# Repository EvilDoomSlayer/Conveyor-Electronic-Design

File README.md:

# Conveyor-Electronic-Design

This repository contains the electronic design automation (EDA) files for the **Luggage Classification Conveyor** custom PCB. It is a submodule of the main firmware repository.

## Overview

This PCB consolidates the connections between the ESP32 microcontroller, the motor drivers, and the various sensors used in the sorting system. It replaces a breadboard setup to provide a robust and reliable connection for the sorting machinery.

## Project Contents

* **/KiCad_Project**: The full project folder containing:
    * `.kicad_sch`: The schematic file.
    * `.kicad_pcb`: The PCB layout file.
* **/Gerbers**: Production files generated for PCB fabrication (Zip file usually required by manufacturers like JLC or PCBWay).

## Schematic Details

The board is designed to interface with an **ESP32-WROOM-32** dev module.

### Key Interfaces
* **Power Input**: 5V DC (Powers the ESP32 and the Servos/DC Motor).
* **Motor Driver**: On-board socket for an **L293D** motor driver IC.
* **Sensor Headers**:
    * 3-pin headers for Servos (Signal, VCC, GND).
    * 4-pin header for HX711 (Load Cell Amplifier).
    * Digital headers for IR (E18-D80NK) and Magnetic (KY-024) sensors.

### Pinout Mapping
This PCB routes the ESP32 GPIOs strictly according to the firmware configuration:

| Component | ESP32 GPIO |
| :--- | :--- |
| **L293D (1A/2A)** | GPIO 16, 17 |
| **Load Cell (SCK/DT)** | GPIO 19, 23 |
| **Servos (1 & 2)** | GPIO 21, 22 |
| **Magnetic Sensor** | GPIO 32 |
| **IR Sensor** | GPIO 34 |

## Fabrication

The design is a 2-layer board. Standard manufacturing tolerances apply:
* **Thickness**: 1.6mm
* **Copper Weight**: 1oz
* **Solder Mask**: Green (or preferred color)

## Software Used

* **KiCad**: For Schematic capture and PCB Layout.

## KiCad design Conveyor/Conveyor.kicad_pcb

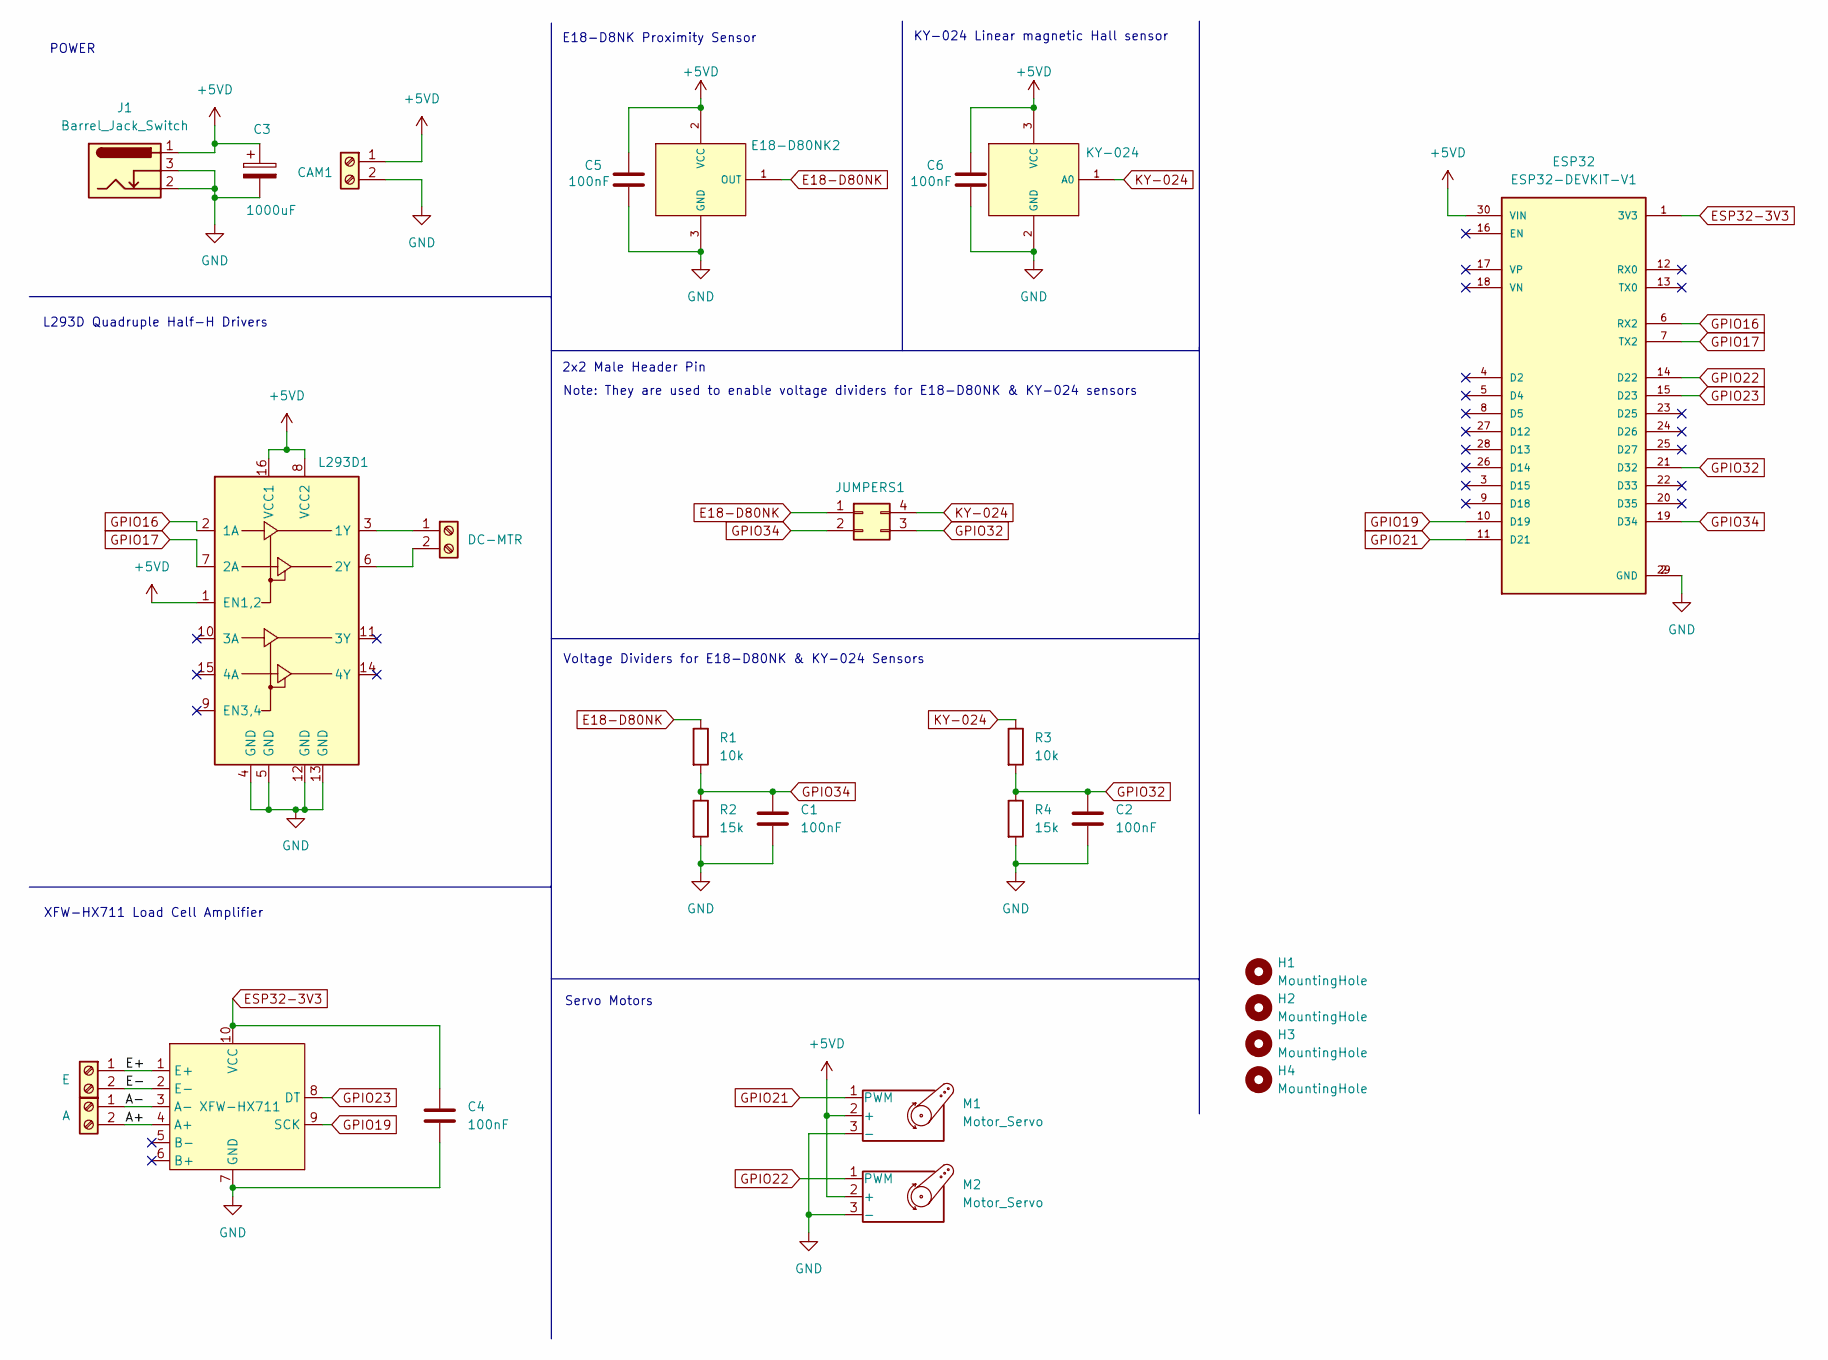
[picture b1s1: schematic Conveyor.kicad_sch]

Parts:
C1, C2, C4, C5, C6: 100nF; C_Disc_D4.3mm_W1.9mm_P5.00mm
C3: 1000uF; CP_Radial_D10.0mm_P5.00mm
CAM1: 5VCC; TerminalBlock_Phoenix_PT-1,5-2-5.0-H_1x02_P5.00mm_Horizontal
E18-D80NK2: E18-D80NK2; PinHeader_1x03_P2.54mm_Vertical
ESP32: ESP32-DEVKIT-V1; MODULE_ESP32_DEVKIT_V1; PARTREV N/A
H1, H2, H3, H4: MountingHole; MountingHole_3.2mm_M3
HX711-A1: A; TerminalBlock_Phoenix_PT-1,5-2-5.0-H_1x02_P5.00mm_Horizontal
HX711-E1: E; TerminalBlock_Phoenix_PT-1,5-2-5.0-H_1x02_P5.00mm_Horizontal
J1: Barrel_Jack_Switch; BarrelJack_Horizontal
JUMPERS1: Header 2x2; PinHeader_2x02_P2.54mm_Vertical
KY-024: KY-024; TerminalBlock_Phoenix_PT-1,5-3-5.0-H_1x03_P5.00mm_Horizontal
L293D1: H-BRIDGE; DIP-16_W7.62mm_Socket
M1, M2: Motor_Servo; PinHeader_1x03_P2.54mm_Vertical
MTR1: DC-MTR; TerminalBlock_Phoenix_PT-1,5-2-5.0-H_1x02_P5.00mm_Horizontal
R1, R3: 10k; R_Axial_DIN0207_L6.3mm_D2.5mm_P10.16mm_Horizontal
R2, R4: 15k; R_Axial_DIN0207_L6.3mm_D2.5mm_P10.16mm_Horizontal
XFW-HX711: HX711; XFW-HX711

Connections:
+5VD: C3.1, C5.1, C6.1, CAM1.1, E18-D80NK2.2 (VCC), ESP32.30 (VIN), J1.1, KY-024.3 (VCC), L293D1.1 (EN1,2), L293D1.8 (VCC2), L293D1.16 (VCC1), M1.2 (+), M2.2 (+)
/A+: HX711-A1.2, XFW-HX711.4 (A+)
/A-: HX711-A1.1, XFW-HX711.3 (A-)
/E+: HX711-E1.1, XFW-HX711.1 (E+)
/E-: HX711-E1.2, XFW-HX711.2 (E-)
E18-D80NK: E18-D80NK2.1 (OUT), JUMPERS1.1, R1.1
ESP32-3V3: C4.1, ESP32.1 (3V3), XFW-HX711.10 (VCC)
GND: C1.2, C2.2, C3.2, C4.2, C5.2, C6.2, CAM1.2, E18-D80NK2.3 (GND), ESP32.2 (GND), ESP32.29 (GND), J1.2, J1.3, KY-024.2 (GND), L293D1.4 (GND), L293D1.5 (GND), L293D1.12 (GND), L293D1.13 (GND), M1.3 (-), M2.3 (-), R2.2, R4.2, XFW-HX711.7 (GND)
GPIO16: ESP32.6 (RX2), L293D1.2 (1A)
GPIO17: ESP32.7 (TX2), L293D1.7 (2A)
GPIO19: ESP32.10 (D19), XFW-HX711.9 (SCK)
GPIO21: ESP32.11 (D21), M1.1 (PWM)
GPIO22: ESP32.14 (D22), M2.1 (PWM)
GPIO23: ESP32.15 (D23), XFW-HX711.8 (DT)
GPIO32: C2.1, ESP32.21 (D32), JUMPERS1.3, R3.2, R4.1
GPIO34: C1.1, ESP32.19 (D34), JUMPERS1.2, R1.2, R2.1
KY-024: JUMPERS1.4, KY-024.1 (A0), R3.1
unnamed: L293D1.3 (1Y), MTR1.1
unnamed: L293D1.6 (2Y), MTR1.2

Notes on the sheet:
E18-D8NK Proximity Sensor
L293D Quadruple Half-H Drivers
KY-024 Linear magnetic Hall sensor
POWER
Servo Motors
Note: They are used to enable voltage dividers for E18-D80NK & KY-024 sensors
Voltage Dividers for E18-D80NK & KY-024 Sensors
2x2 Male Header Pin
XFW-HX711 Load Cell Amplifier

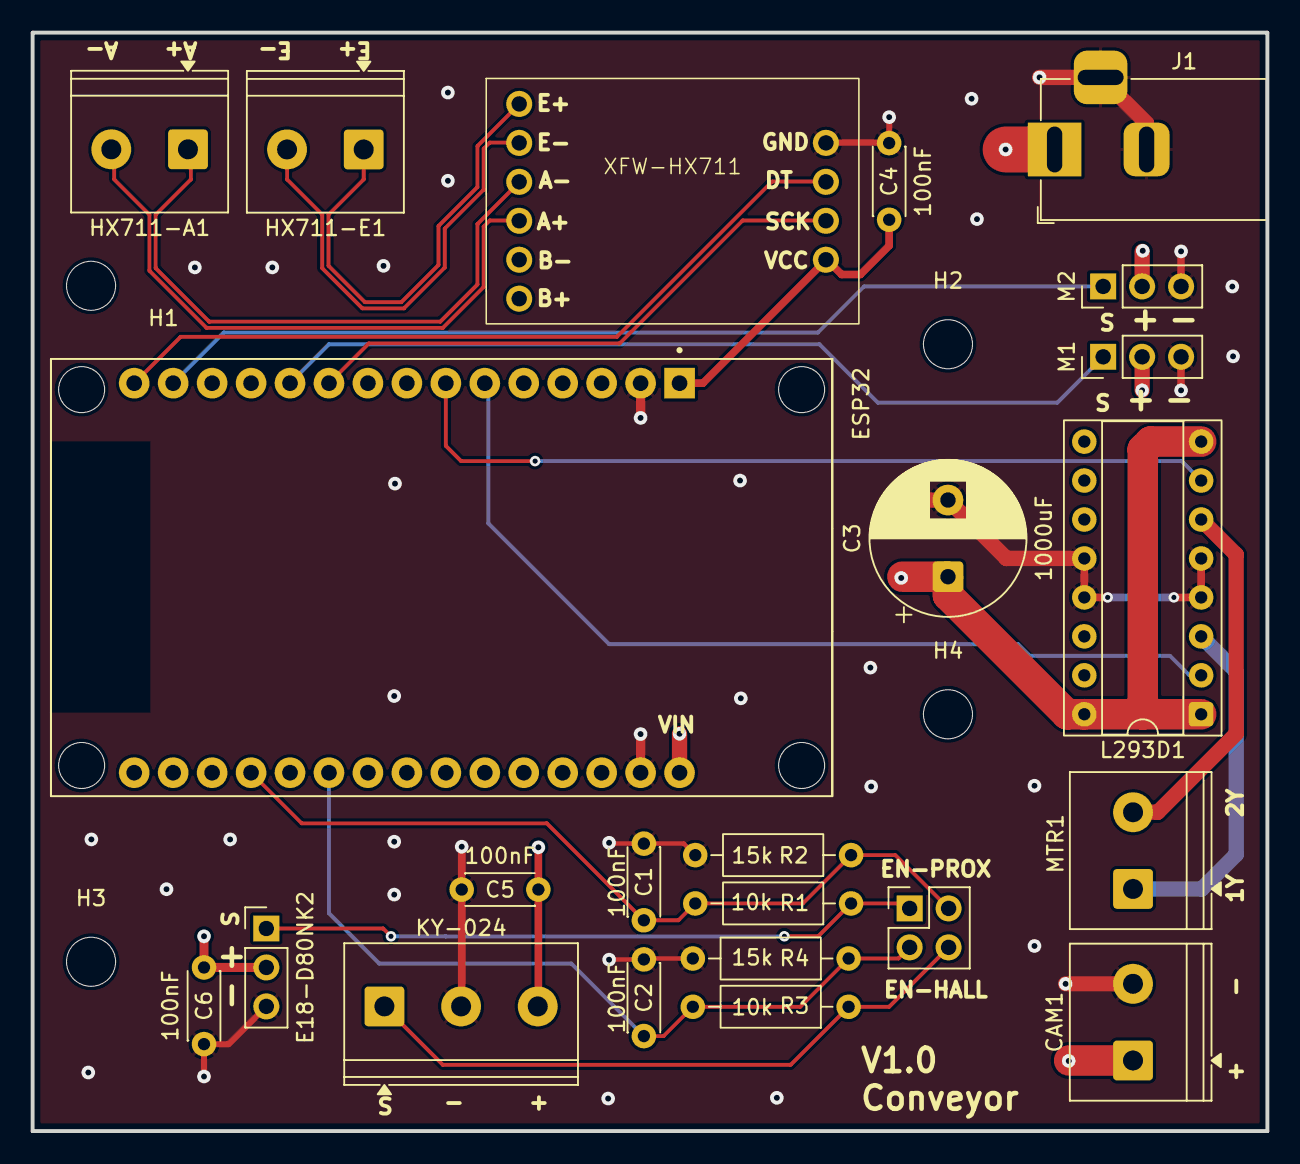
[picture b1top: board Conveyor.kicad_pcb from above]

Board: 4 copper layers, 80.5 x 71.6 mm, 27 parts (0 on the bottom side), 19 nets.

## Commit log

2025-10-27 Added Kicad proyect
2025-12-04 Actualizar README.md
